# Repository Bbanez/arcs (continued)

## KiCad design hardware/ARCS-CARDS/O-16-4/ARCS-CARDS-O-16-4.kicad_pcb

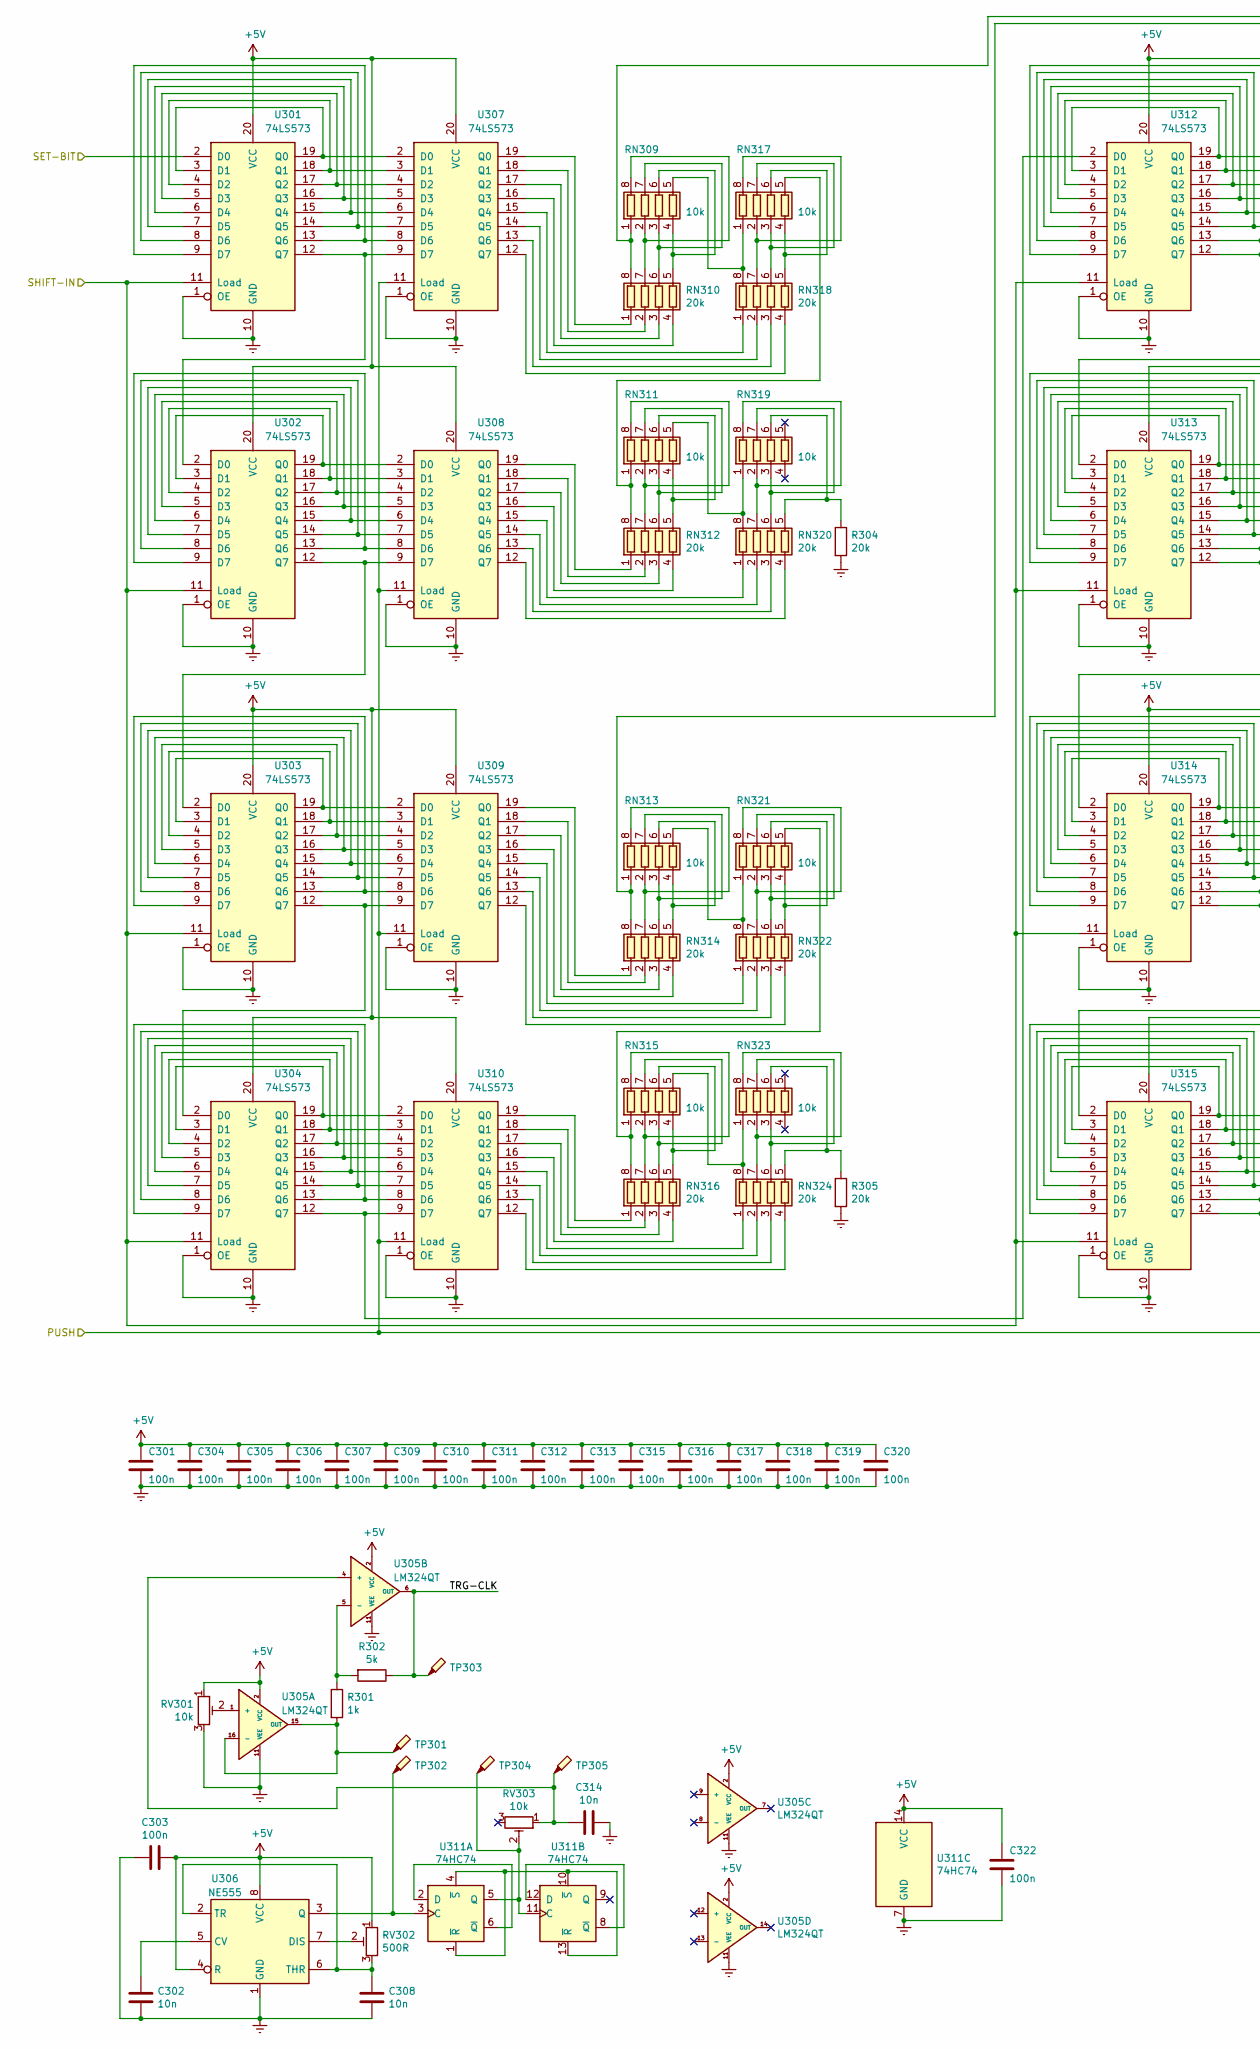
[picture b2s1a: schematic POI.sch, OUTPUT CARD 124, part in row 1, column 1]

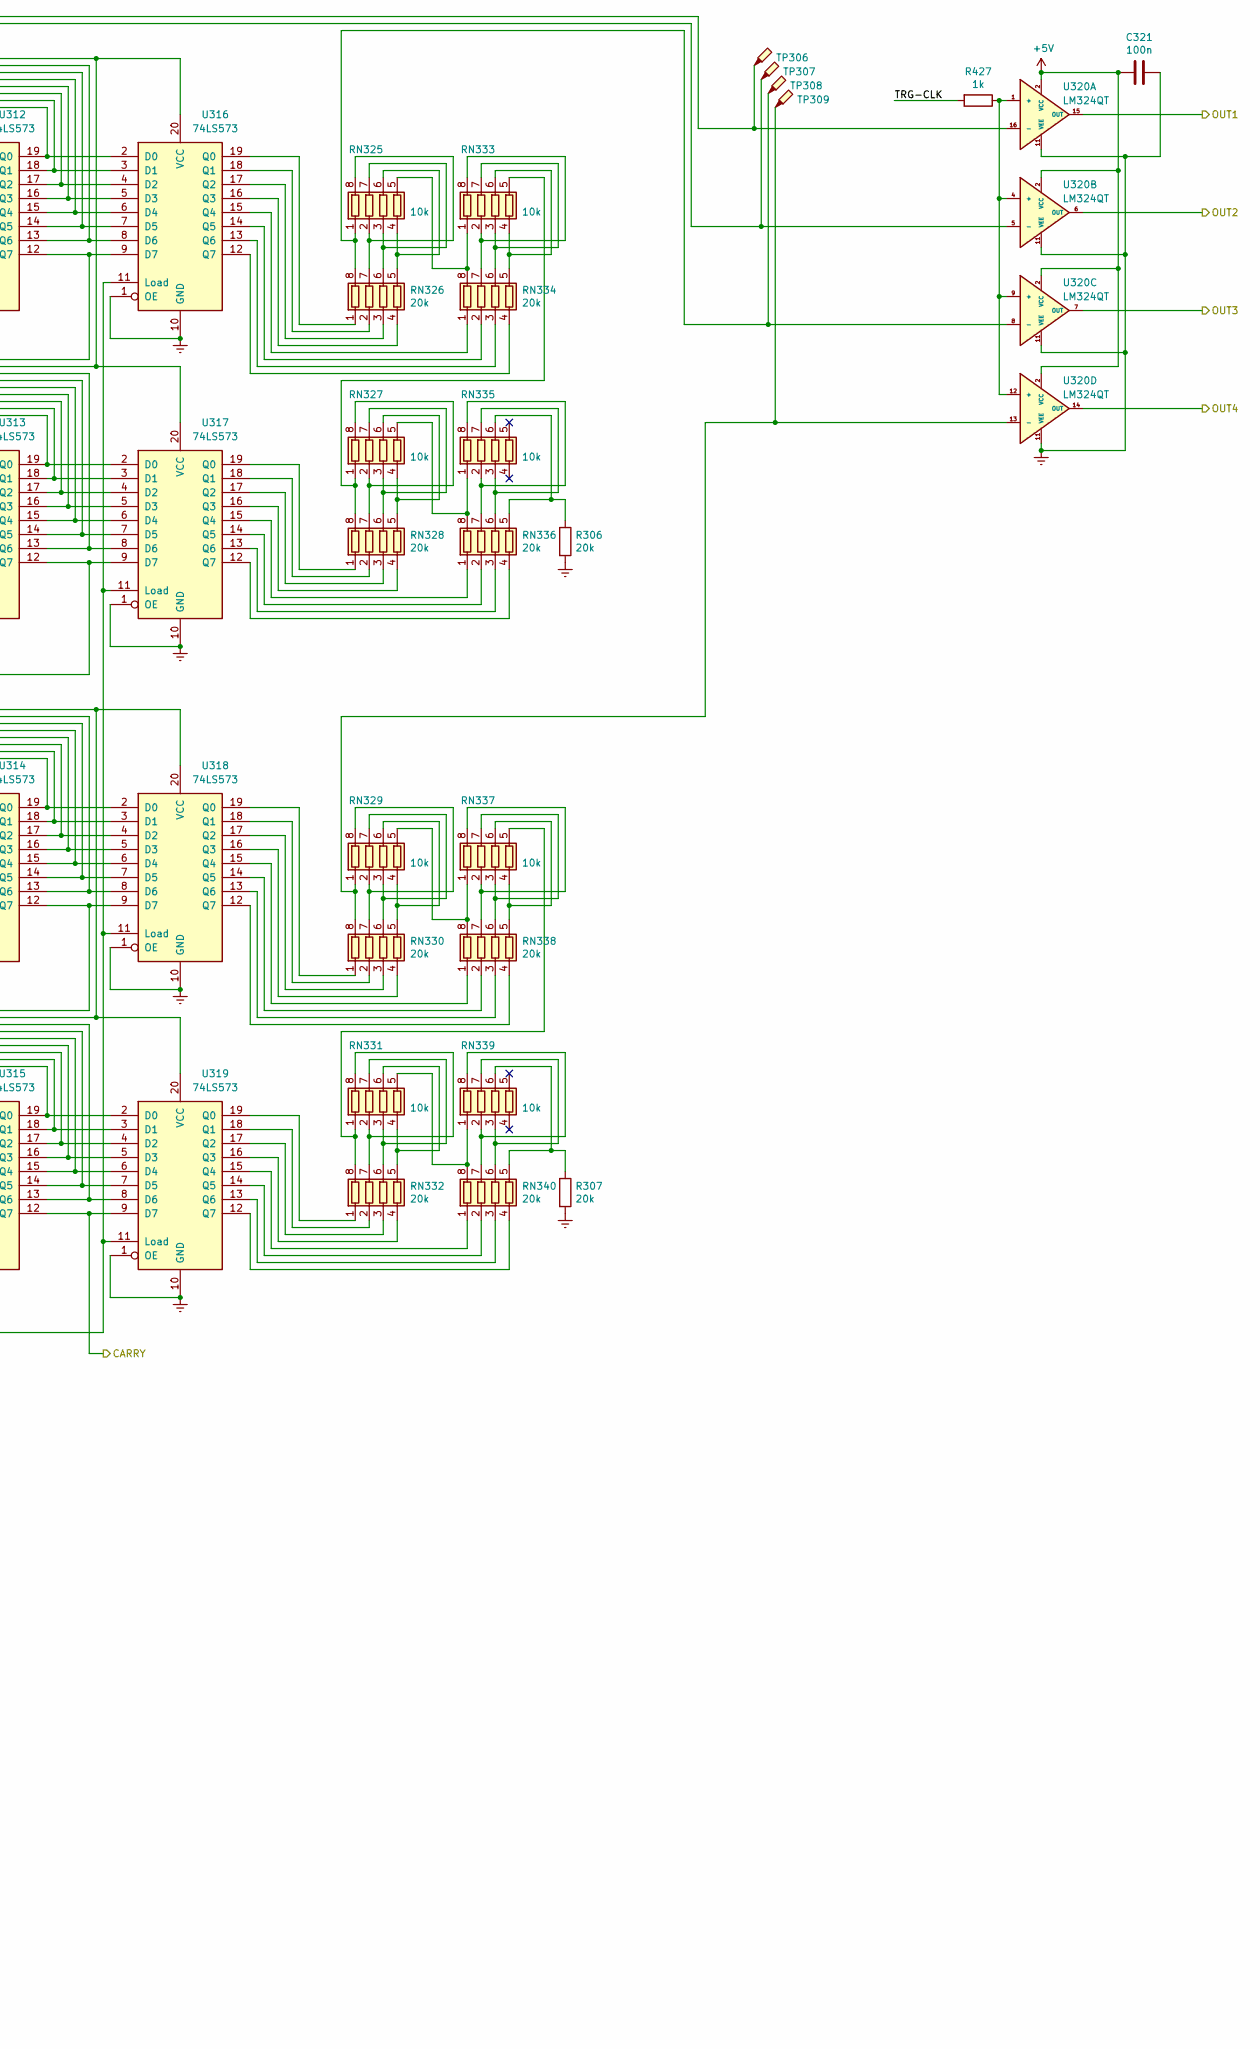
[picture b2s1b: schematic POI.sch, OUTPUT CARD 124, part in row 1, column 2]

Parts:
C301, C303, C304, C305, C306, C307, C309, C310, C311, C312, C313, C315, C316, C317, C318, C319, C320, C321, C322: 100n; C_0603_1608Metric
C302, C308, C314: 10n; C_0603_1608Metric
R301, R427: 1k; R_0603_1608Metric
R302: 5k; R_0603_1608Metric
R304, R305, R306, R307: 20k; R_0603_1608Metric
RN309, RN311, RN313, RN315, RN317, RN319, RN321, RN323, RN325, RN327, RN329, RN331, RN333, RN335, RN337, RN339: 10k; R_Array_Convex_4x0603
RN310, RN312, RN314, RN316, RN318, RN320, RN322, RN324, RN326, RN328, RN330, RN332, RN334, RN336, RN338, RN340: 20k; R_Array_Convex_4x0603
RV301, RV303: 10k; Potentiometer_Bourns_3224W_Vertical
RV302: 500R; Potentiometer_Bourns_3224W_Vertical
TP301, TP302, TP303, TP304, TP305, TP306, TP307, TP308, TP309: TestPoint_Probe; TestPoint_Pad_D1.0mm
U301, U302, U303, U304, U307, U308, U309, U310, U312, U313, U314, U315, U316, U317, U318, U319: 74LS573; TSSOP-20_4.4x6.5mm_P0.65mm
U305, U320: LM324QT; QFN-16-1EP_3x3mm_P0.5mm_EP1.8x1.8mm
U306: NE555; TSSOP-8_3x3mm_P0.65mm
U311: 74HC74; TSSOP-14_4.4x5mm_P0.65mm

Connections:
+5V: C301.1, C303.1, C304.1, C305.1, C306.1, C307.1, C309.1, C310.1, C311.1, C312.1, C313.1, C315.1, C316.1, C317.1, C318.1, C319.1, C320.1, C321.2, C322.1, RV301.1, RV302.1, U301.20 (VCC), U302.20 (VCC), U303.20 (VCC), U304.20 (VCC), U305.2 (VCC), U306.4 (R), U306.8 (VCC), U307.20 (VCC), U308.20 (VCC), U309.20 (VCC), U310.20 (VCC), U311.14 (VCC), U312.20 (VCC), U313.20 (VCC), U314.20 (VCC), U315.20 (VCC), U316.20 (VCC), U317.20 (VCC), U318.20 (VCC), U319.20 (VCC), U320.2 (VCC); also elsewhere on the board
/PWM OUTPUT INTERFACE/CARRY: U315.12 (Q7), U319.9 (D7); also elsewhere on the board
/PWM OUTPUT INTERFACE/OUT1: U320.15 (OUT); also elsewhere on the board
/PWM OUTPUT INTERFACE/OUT2: U320.6 (OUT); also elsewhere on the board
/PWM OUTPUT INTERFACE/OUT3: U320.7 (OUT); also elsewhere on the board
/PWM OUTPUT INTERFACE/OUT4: U320.14 (OUT); also elsewhere on the board
/PWM OUTPUT INTERFACE/PUSH: U307.11 (Load), U308.11 (Load), U309.11 (Load), U310.11 (Load), U316.11 (Load), U317.11 (Load), U318.11 (Load), U319.11 (Load); also elsewhere on the board
/PWM OUTPUT INTERFACE/SET-BIT: U301.2 (D0); also elsewhere on the board
/PWM OUTPUT INTERFACE/SHIFT-IN: U301.11 (Load), U302.11 (Load), U303.11 (Load), U304.11 (Load), U312.11 (Load), U313.11 (Load), U314.11 (Load), U315.11 (Load); also elsewhere on the board
/PWM OUTPUT INTERFACE/TRG-CLK: R302.1, R427.2, TP303.1, U305.6 (OUT)
Earth: C301.2, C302.2, C303.2, C304.2, C305.2, C306.2, C307.2, C308.2, C309.2, C310.2, C311.2, C312.2, C313.2, C314.1, C315.2, C316.2, C317.2, C318.2, C319.2, C320.2, C321.1, C322.2, R304.2, R305.2, R306.2, R307.2, RV301.3, U301.1 (OE), U301.10 (GND), U302.1 (OE), U302.10 (GND), U303.1 (OE), U303.10 (GND), U304.1 (OE), U304.10 (GND), U305.11 (VEE), U306.1 (GND), U307.1 (OE), U307.10 (GND), U308.1 (OE), U308.10 (GND), U309.1 (OE), U309.10 (GND), U310.1 (OE), U310.10 (GND), U311.7 (GND), U312.1 (OE), U312.10 (GND), U313.1 (OE), U313.10 (GND), U314.1 (OE), U314.10 (GND), U315.1 (OE), U315.10 (GND), U316.1 (OE), U316.10 (GND), U317.1 (OE), U317.10 (GND), U318.1 (OE), U318.10 (GND), U319.1 (OE), U319.10 (GND), U320.11 (VEE); also elsewhere on the board
unnamed: C302.1, U306.5 (CV)
unnamed: C308.1, RV302.3, U306.2 (TR), U306.6 (THR)
unnamed: C314.2, RV303.1, TP305.1, U305.4 (+)
unnamed: R301.1, R302.2, U305.5 (-)
unnamed: R301.2, TP301.1, U305.15 (OUT), U305.16 (-)
unnamed: R304.1, RN319.6 (R3.2), RN320.5 (R4.2)
unnamed: R305.1, RN323.6 (R3.2), RN324.5 (R4.2)
unnamed: R306.1, RN335.6 (R3.2), RN336.5 (R4.2)
unnamed: R307.1, RN339.6 (R3.2), RN340.5 (R4.2)
unnamed: R427.1, U320.1 (+), U320.4 (+), U320.9 (+), U320.12 (+)
unnamed: RN309.1 (R1.1), RN310.8 (R1.2), TP306.1, U320.16 (-)
unnamed: RN309.2 (R2.1), RN309.8 (R1.2), RN310.7 (R2.2)
unnamed: RN309.3 (R3.1), RN309.7 (R2.2), RN310.6 (R3.2)
unnamed: RN309.4 (R4.1), RN309.6 (R3.2), RN310.5 (R4.2)
unnamed: RN309.5 (R4.2), RN317.1 (R1.1), RN318.8 (R1.2)
unnamed: RN310.1 (R1.1), U307.19 (Q0)
unnamed: RN310.2 (R2.1), U307.18 (Q1)
unnamed: RN310.3 (R3.1), U307.17 (Q2)
unnamed: RN310.4 (R4.1), U307.16 (Q3)
unnamed: RN311.1 (R1.1), RN312.8 (R1.2), RN317.5 (R4.2)
unnamed: RN311.2 (R2.1), RN311.8 (R1.2), RN312.7 (R2.2)
unnamed: RN311.3 (R3.1), RN311.7 (R2.2), RN312.6 (R3.2)
unnamed: RN311.4 (R4.1), RN311.6 (R3.2), RN312.5 (R4.2)
unnamed: RN311.5 (R4.2), RN319.1 (R1.1), RN320.8 (R1.2)
unnamed: RN312.1 (R1.1), U308.19 (Q0)
unnamed: RN312.2 (R2.1), U308.18 (Q1)
unnamed: RN312.3 (R3.1), U308.17 (Q2)
unnamed: RN312.4 (R4.1), U308.16 (Q3)
unnamed: RN313.1 (R1.1), RN314.8 (R1.2), TP307.1, U320.5 (-)
unnamed: RN313.2 (R2.1), RN313.8 (R1.2), RN314.7 (R2.2)
unnamed: RN313.3 (R3.1), RN313.7 (R2.2), RN314.6 (R3.2)
unnamed: RN313.4 (R4.1), RN313.6 (R3.2), RN314.5 (R4.2)
unnamed: RN313.5 (R4.2), RN321.1 (R1.1), RN322.8 (R1.2)
unnamed: RN314.1 (R1.1), U309.19 (Q0)
unnamed: RN314.2 (R2.1), U309.18 (Q1)
unnamed: RN314.3 (R3.1), U309.17 (Q2)
unnamed: RN314.4 (R4.1), U309.16 (Q3)
unnamed: RN315.1 (R1.1), RN316.8 (R1.2), RN321.5 (R4.2)
unnamed: RN315.2 (R2.1), RN315.8 (R1.2), RN316.7 (R2.2)
unnamed: RN315.3 (R3.1), RN315.7 (R2.2), RN316.6 (R3.2)
unnamed: RN315.4 (R4.1), RN315.6 (R3.2), RN316.5 (R4.2)
unnamed: RN315.5 (R4.2), RN323.1 (R1.1), RN324.8 (R1.2)
unnamed: RN316.1 (R1.1), U310.19 (Q0)
unnamed: RN316.2 (R2.1), U310.18 (Q1)
unnamed: RN316.3 (R3.1), U310.17 (Q2)
unnamed: RN316.4 (R4.1), U310.16 (Q3)
unnamed: RN317.2 (R2.1), RN317.8 (R1.2), RN318.7 (R2.2)
unnamed: RN317.3 (R3.1), RN317.7 (R2.2), RN318.6 (R3.2)
unnamed: RN317.4 (R4.1), RN317.6 (R3.2), RN318.5 (R4.2)
unnamed: RN318.1 (R1.1), U307.15 (Q4)
unnamed: RN318.2 (R2.1), U307.14 (Q5)
unnamed: RN318.3 (R3.1), U307.13 (Q6)
unnamed: RN318.4 (R4.1), U307.12 (Q7)
unnamed: RN319.2 (R2.1), RN319.8 (R1.2), RN320.7 (R2.2)
unnamed: RN319.3 (R3.1), RN319.7 (R2.2), RN320.6 (R3.2)
unnamed: RN320.1 (R1.1), U308.15 (Q4)
unnamed: RN320.2 (R2.1), U308.14 (Q5)
unnamed: RN320.3 (R3.1), U308.13 (Q6)
unnamed: RN320.4 (R4.1), U308.12 (Q7)
unnamed: RN321.2 (R2.1), RN321.8 (R1.2), RN322.7 (R2.2)
unnamed: RN321.3 (R3.1), RN321.7 (R2.2), RN322.6 (R3.2)
unnamed: RN321.4 (R4.1), RN321.6 (R3.2), RN322.5 (R4.2)
unnamed: RN322.1 (R1.1), U309.15 (Q4)
unnamed: RN322.2 (R2.1), U309.14 (Q5)
unnamed: RN322.3 (R3.1), U309.13 (Q6)
unnamed: RN322.4 (R4.1), U309.12 (Q7)
unnamed: RN323.2 (R2.1), RN323.8 (R1.2), RN324.7 (R2.2)
unnamed: RN323.3 (R3.1), RN323.7 (R2.2), RN324.6 (R3.2)
unnamed: RN324.1 (R1.1), U310.15 (Q4)
unnamed: RN324.2 (R2.1), U310.14 (Q5)
unnamed: RN324.3 (R3.1), U310.13 (Q6)
unnamed: RN324.4 (R4.1), U310.12 (Q7)
unnamed: RN325.1 (R1.1), RN326.8 (R1.2), TP308.1, U320.8 (-)
unnamed: RN325.2 (R2.1), RN325.8 (R1.2), RN326.7 (R2.2)
unnamed: RN325.3 (R3.1), RN325.7 (R2.2), RN326.6 (R3.2)
unnamed: RN325.4 (R4.1), RN325.6 (R3.2), RN326.5 (R4.2)
unnamed: RN325.5 (R4.2), RN333.1 (R1.1), RN334.8 (R1.2)
unnamed: RN326.1 (R1.1), U316.19 (Q0)
unnamed: RN326.2 (R2.1), U316.18 (Q1)
unnamed: RN326.3 (R3.1), U316.17 (Q2)
unnamed: RN326.4 (R4.1), U316.16 (Q3)
unnamed: RN327.1 (R1.1), RN328.8 (R1.2), RN333.5 (R4.2)
unnamed: RN327.2 (R2.1), RN327.8 (R1.2), RN328.7 (R2.2)
unnamed: RN327.3 (R3.1), RN327.7 (R2.2), RN328.6 (R3.2)
unnamed: RN327.4 (R4.1), RN327.6 (R3.2), RN328.5 (R4.2)
unnamed: RN327.5 (R4.2), RN335.1 (R1.1), RN336.8 (R1.2)
unnamed: RN328.1 (R1.1), U317.19 (Q0)
unnamed: RN328.2 (R2.1), U317.18 (Q1)
unnamed: RN328.3 (R3.1), U317.17 (Q2)
unnamed: RN328.4 (R4.1), U317.16 (Q3)
unnamed: RN329.1 (R1.1), RN330.8 (R1.2), TP309.1, U320.13 (-)
unnamed: RN329.2 (R2.1), RN329.8 (R1.2), RN330.7 (R2.2)
unnamed: RN329.3 (R3.1), RN329.7 (R2.2), RN330.6 (R3.2)
unnamed: RN329.4 (R4.1), RN329.6 (R3.2), RN330.5 (R4.2)
unnamed: RN329.5 (R4.2), RN337.1 (R1.1), RN338.8 (R1.2)
unnamed: RN330.1 (R1.1), U318.19 (Q0)
unnamed: RN330.2 (R2.1), U318.18 (Q1)
unnamed: RN330.3 (R3.1), U318.17 (Q2)
unnamed: RN330.4 (R4.1), U318.16 (Q3)
unnamed: RN331.1 (R1.1), RN332.8 (R1.2), RN337.5 (R4.2)
unnamed: RN331.2 (R2.1), RN331.8 (R1.2), RN332.7 (R2.2)
unnamed: RN331.3 (R3.1), RN331.7 (R2.2), RN332.6 (R3.2)
unnamed: RN331.4 (R4.1), RN331.6 (R3.2), RN332.5 (R4.2)
unnamed: RN331.5 (R4.2), RN339.1 (R1.1), RN340.8 (R1.2)
unnamed: RN332.1 (R1.1), U319.19 (Q0)
unnamed: RN332.2 (R2.1), U319.18 (Q1)
unnamed: RN332.3 (R3.1), U319.17 (Q2)
unnamed: RN332.4 (R4.1), U319.16 (Q3)
unnamed: RN333.2 (R2.1), RN333.8 (R1.2), RN334.7 (R2.2)
unnamed: RN333.3 (R3.1), RN333.7 (R2.2), RN334.6 (R3.2)
unnamed: RN333.4 (R4.1), RN333.6 (R3.2), RN334.5 (R4.2)
unnamed: RN334.1 (R1.1), U316.15 (Q4)
unnamed: RN334.2 (R2.1), U316.14 (Q5)
unnamed: RN334.3 (R3.1), U316.13 (Q6)
unnamed: RN334.4 (R4.1), U316.12 (Q7)
unnamed: RN335.2 (R2.1), RN335.8 (R1.2), RN336.7 (R2.2)
unnamed: RN335.3 (R3.1), RN335.7 (R2.2), RN336.6 (R3.2)
unnamed: RN336.1 (R1.1), U317.15 (Q4)
unnamed: RN336.2 (R2.1), U317.14 (Q5)
unnamed: RN336.3 (R3.1), U317.13 (Q6)
unnamed: RN336.4 (R4.1), U317.12 (Q7)
unnamed: RN337.2 (R2.1), RN337.8 (R1.2), RN338.7 (R2.2)
unnamed: RN337.3 (R3.1), RN337.7 (R2.2), RN338.6 (R3.2)
unnamed: RN337.4 (R4.1), RN337.6 (R3.2), RN338.5 (R4.2)
unnamed: RN338.1 (R1.1), U318.15 (Q4)
unnamed: RN338.2 (R2.1), U318.14 (Q5)
unnamed: RN338.3 (R3.1), U318.13 (Q6)
unnamed: RN338.4 (R4.1), U318.12 (Q7)
unnamed: RN339.2 (R2.1), RN339.8 (R1.2), RN340.7 (R2.2)
unnamed: RN339.3 (R3.1), RN339.7 (R2.2), RN340.6 (R3.2)
unnamed: RN340.1 (R1.1), U319.15 (Q4)
unnamed: RN340.2 (R2.1), U319.14 (Q5)
unnamed: RN340.3 (R3.1), U319.13 (Q6)
unnamed: RN340.4 (R4.1), U319.12 (Q7)
unnamed: RV301.2, U305.1 (+)
unnamed: RV302.2, U306.7 (DIS)
unnamed: RV303.2, TP304.1, U311.5 (Q), U311.11 (C)
unnamed: TP302.1, U306.3 (Q), U311.3 (C)
unnamed: U301.12 (Q7), U302.2 (D0), U307.9 (D7)
unnamed: U301.9 (D7), U301.13 (Q6), U307.8 (D6)
unnamed: U301.8 (D6), U301.14 (Q5), U307.7 (D5)
unnamed: U301.7 (D5), U301.15 (Q4), U307.6 (D4)
unnamed: U301.6 (D4), U301.16 (Q3), U307.5 (D3)
unnamed: U301.5 (D3), U301.17 (Q2), U307.4 (D2)
unnamed: U301.4 (D2), U301.18 (Q1), U307.3 (D1)
unnamed: U301.3 (D1), U301.19 (Q0), U307.2 (D0)
unnamed: U302.12 (Q7), U303.2 (D0), U308.9 (D7)
unnamed: U302.9 (D7), U302.13 (Q6), U308.8 (D6)
unnamed: U302.8 (D6), U302.14 (Q5), U308.7 (D5)
unnamed: U302.7 (D5), U302.15 (Q4), U308.6 (D4)
unnamed: U302.6 (D4), U302.16 (Q3), U308.5 (D3)
unnamed: U302.5 (D3), U302.17 (Q2), U308.4 (D2)
unnamed: U302.4 (D2), U302.18 (Q1), U308.3 (D1)
unnamed: U302.3 (D1), U302.19 (Q0), U308.2 (D0)
unnamed: U303.12 (Q7), U304.2 (D0), U309.9 (D7)
unnamed: U303.9 (D7), U303.13 (Q6), U309.8 (D6)
unnamed: U303.8 (D6), U303.14 (Q5), U309.7 (D5)
unnamed: U303.7 (D5), U303.15 (Q4), U309.6 (D4)
unnamed: U303.6 (D4), U303.16 (Q3), U309.5 (D3)
unnamed: U303.5 (D3), U303.17 (Q2), U309.4 (D2)
unnamed: U303.4 (D2), U303.18 (Q1), U309.3 (D1)
unnamed: U303.3 (D1), U303.19 (Q0), U309.2 (D0)
unnamed: U304.12 (Q7), U310.9 (D7), U312.2 (D0)
unnamed: U304.9 (D7), U304.13 (Q6), U310.8 (D6)
unnamed: U304.8 (D6), U304.14 (Q5), U310.7 (D5)
unnamed: U304.7 (D5), U304.15 (Q4), U310.6 (D4)
unnamed: U304.6 (D4), U304.16 (Q3), U310.5 (D3)
unnamed: U304.5 (D3), U304.17 (Q2), U310.4 (D2)
unnamed: U304.4 (D2), U304.18 (Q1), U310.3 (D1)
unnamed: U304.3 (D1), U304.19 (Q0), U310.2 (D0)
unnamed: U311.1 (~R), U311.4 (~S), U311.10 (~S), U311.13 (~R)
unnamed: U311.2 (D), U311.6 (~Q)
unnamed: U311.8 (~Q), U311.12 (D)
unnamed: U312.12 (Q7), U313.2 (D0), U316.9 (D7)
unnamed: U312.9 (D7), U312.13 (Q6), U316.8 (D6)
unnamed: U312.8 (D6), U312.14 (Q5), U316.7 (D5)
unnamed: U312.7 (D5), U312.15 (Q4), U316.6 (D4)
unnamed: U312.6 (D4), U312.16 (Q3), U316.5 (D3)
unnamed: U312.5 (D3), U312.17 (Q2), U316.4 (D2)
unnamed: U312.4 (D2), U312.18 (Q1), U316.3 (D1)
unnamed: U312.3 (D1), U312.19 (Q0), U316.2 (D0)
unnamed: U313.12 (Q7), U314.2 (D0), U317.9 (D7)
unnamed: U313.9 (D7), U313.13 (Q6), U317.8 (D6)
unnamed: U313.8 (D6), U313.14 (Q5), U317.7 (D5)
unnamed: U313.7 (D5), U313.15 (Q4), U317.6 (D4)
unnamed: U313.6 (D4), U313.16 (Q3), U317.5 (D3)
unnamed: U313.5 (D3), U313.17 (Q2), U317.4 (D2)
unnamed: U313.4 (D2), U313.18 (Q1), U317.3 (D1)
unnamed: U313.3 (D1), U313.19 (Q0), U317.2 (D0)
unnamed: U314.12 (Q7), U315.2 (D0), U318.9 (D7)
unnamed: U314.9 (D7), U314.13 (Q6), U318.8 (D6)
unnamed: U314.8 (D6), U314.14 (Q5), U318.7 (D5)
unnamed: U314.7 (D5), U314.15 (Q4), U318.6 (D4)
unnamed: U314.6 (D4), U314.16 (Q3), U318.5 (D3)
unnamed: U314.5 (D3), U314.17 (Q2), U318.4 (D2)
unnamed: U314.4 (D2), U314.18 (Q1), U318.3 (D1)
unnamed: U314.3 (D1), U314.19 (Q0), U318.2 (D0)
unnamed: U315.9 (D7), U315.13 (Q6), U319.8 (D6)
unnamed: U315.8 (D6), U315.14 (Q5), U319.7 (D5)
unnamed: U315.7 (D5), U315.15 (Q4), U319.6 (D4)
unnamed: U315.6 (D4), U315.16 (Q3), U319.5 (D3)
unnamed: U315.5 (D3), U315.17 (Q2), U319.4 (D2)
unnamed: U315.4 (D2), U315.18 (Q1), U319.3 (D1)
unnamed: U315.3 (D1), U315.19 (Q0), U319.2 (D0)

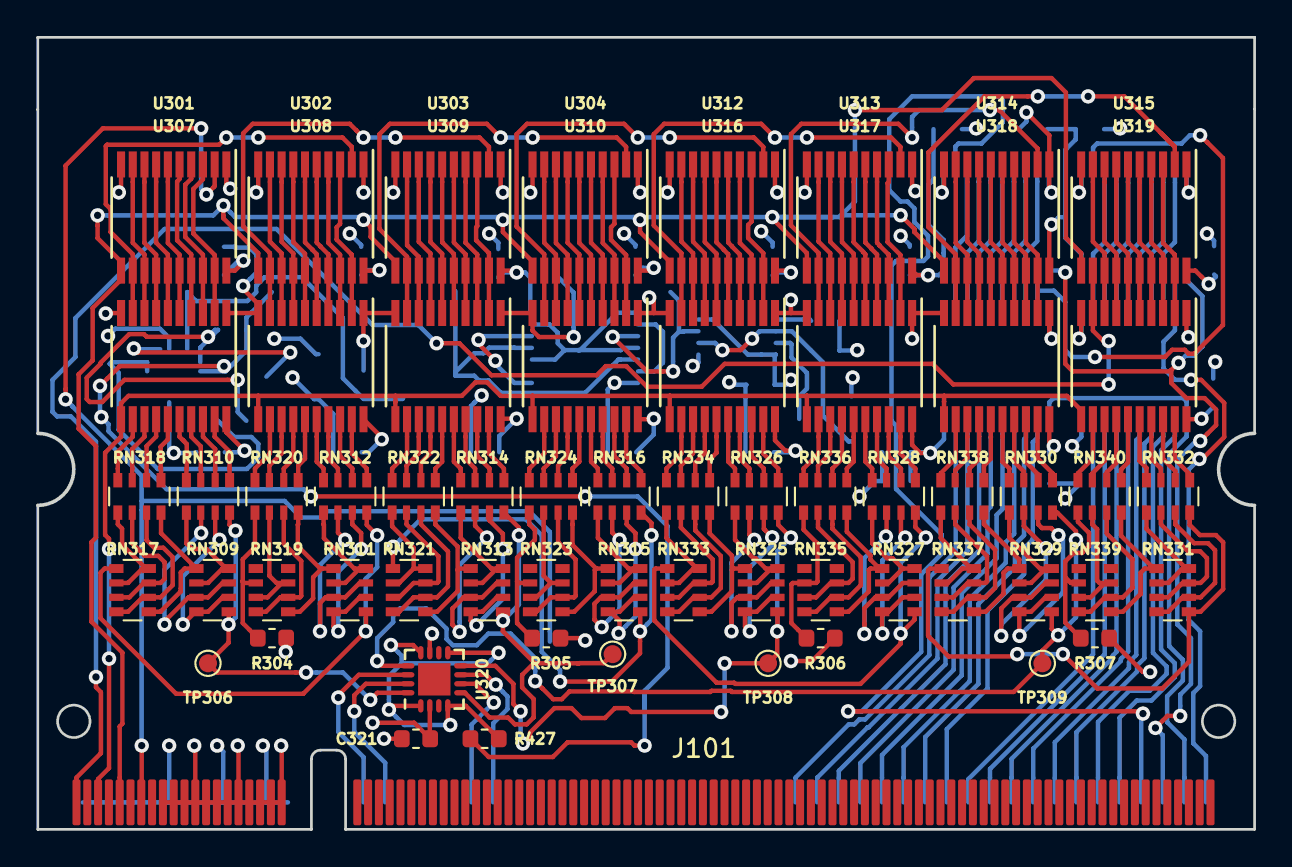
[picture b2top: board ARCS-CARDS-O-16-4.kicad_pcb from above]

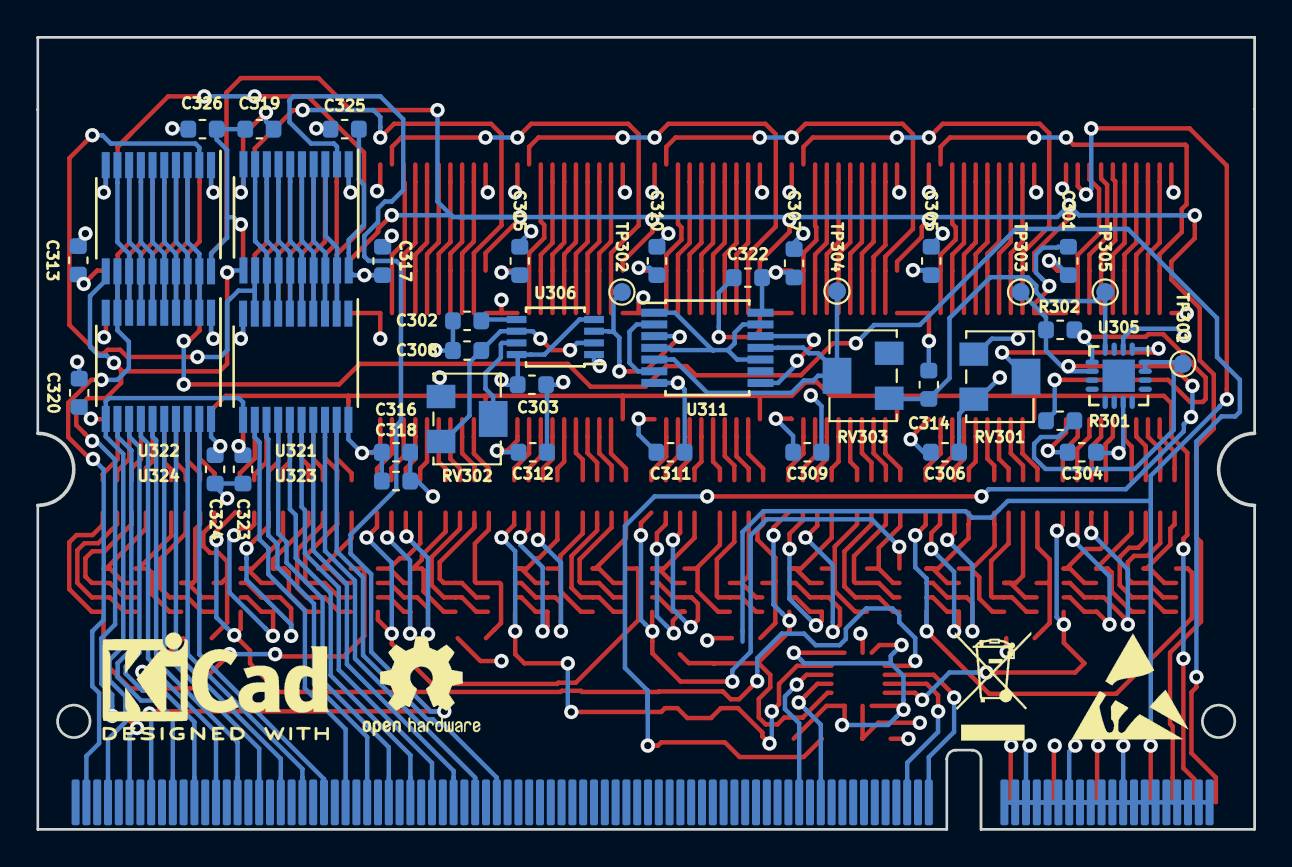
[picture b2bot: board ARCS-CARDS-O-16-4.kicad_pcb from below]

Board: 4 copper layers, 67.6 x 44.0 mm, 102 parts (42 on the bottom side), 250 nets.

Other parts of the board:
C323, C324, C325, C326: 100n; C_0603_1608Metric
J101: SODIMM-200; SODIMM-200PINS
U321, U322, U323, U324: 74HC573; TSSOP-20_4.4x6.5mm_P0.65mm

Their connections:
+5V: C323.1, C324.1, C325.1, C326.1, J101.9, J101.10, J101.11, J101.12, J101.13, J101.14, J101.15, J101.16, J101.17, J101.18, J101.19, J101.20, U321.20, U322.20, U323.20, U324.20; also elsewhere on the board
/DIGITAL OUTPUT INTERFACE/CARRY: J101.199, U322.12, U324.9
/DIGITAL OUTPUT INTERFACE/OUT1: J101.161, U323.19
/DIGITAL OUTPUT INTERFACE/OUT2: J101.163, U323.18
/DIGITAL OUTPUT INTERFACE/OUT3: J101.165, U323.17
/DIGITAL OUTPUT INTERFACE/OUT4: J101.167, U323.16
/DIGITAL OUTPUT INTERFACE/OUT5: J101.169, U323.15
/DIGITAL OUTPUT INTERFACE/OUT6: J101.171, U323.14
/DIGITAL OUTPUT INTERFACE/OUT7: J101.173, U323.13
/DIGITAL OUTPUT INTERFACE/OUT8: J101.175, U323.12
/DIGITAL OUTPUT INTERFACE/OUT9: J101.177, U324.19
/DIGITAL OUTPUT INTERFACE/OUT10: J101.179, U324.18
/DIGITAL OUTPUT INTERFACE/OUT11: J101.181, U324.17
/DIGITAL OUTPUT INTERFACE/OUT12: J101.183, U324.16
/DIGITAL OUTPUT INTERFACE/OUT13: J101.185, U324.15
/DIGITAL OUTPUT INTERFACE/OUT14: J101.187, U324.14
/DIGITAL OUTPUT INTERFACE/OUT15: J101.189, U324.13
/DIGITAL OUTPUT INTERFACE/OUT16: J101.191, U324.12
/DIGITAL OUTPUT INTERFACE/PUSH: J101.197, U323.11, U324.11
/DIGITAL OUTPUT INTERFACE/SET-BIT: J101.193, U321.2
/DIGITAL OUTPUT INTERFACE/SHIFT-IN: J101.195, U321.11, U322.11
/PWM OUTPUT INTERFACE/CARRY: J101.1; also elsewhere on the board
/PWM OUTPUT INTERFACE/OUT1: J101.123; also elsewhere on the board
/PWM OUTPUT INTERFACE/OUT2: J101.131; also elsewhere on the board
/PWM OUTPUT INTERFACE/OUT3: J101.133; also elsewhere on the board
/PWM OUTPUT INTERFACE/OUT4: J101.121; also elsewhere on the board
/PWM OUTPUT INTERFACE/PUSH: J101.3; also elsewhere on the board
/PWM OUTPUT INTERFACE/SET-BIT: J101.7; also elsewhere on the board
/PWM OUTPUT INTERFACE/SHIFT-IN: J101.5; also elsewhere on the board
Earth: C323.2, C324.2, C325.2, C326.2, J101.21, J101.22, J101.23, J101.24, J101.25, J101.26, J101.27, J101.28, J101.29, J101.30, J101.31, J101.32, J101.33, J101.34, J101.35, J101.36, J101.37, J101.38, J101.39, J101.40, U321.1, U321.10, U322.1, U322.10, U323.1, U323.10, U324.1, U324.10; also elsewhere on the board
unnamed: U321.12, U322.2, U323.9
unnamed: U321.9, U321.13, U323.8
unnamed: U321.8, U321.14, U323.7
unnamed: U321.7, U321.15, U323.6
unnamed: U321.6, U321.16, U323.5
unnamed: U321.5, U321.17, U323.4
unnamed: U321.4, U321.18, U323.3
unnamed: U321.3, U321.19, U323.2
unnamed: U322.9, U322.13, U324.8
unnamed: U322.8, U322.14, U324.7
unnamed: U322.7, U322.15, U324.6
unnamed: U322.6, U322.16, U324.5
unnamed: U322.5, U322.17, U324.4
unnamed: U322.4, U322.18, U324.3
unnamed: U322.3, U322.19, U324.2

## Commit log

2018-10-07 Setup
2019-03-30 Make changes to STM32F103C8 and add STM32F103VE based PD system.
2019-04-03 Create cards for input and output interface.
2019-04-05 Create analog input interface card.
